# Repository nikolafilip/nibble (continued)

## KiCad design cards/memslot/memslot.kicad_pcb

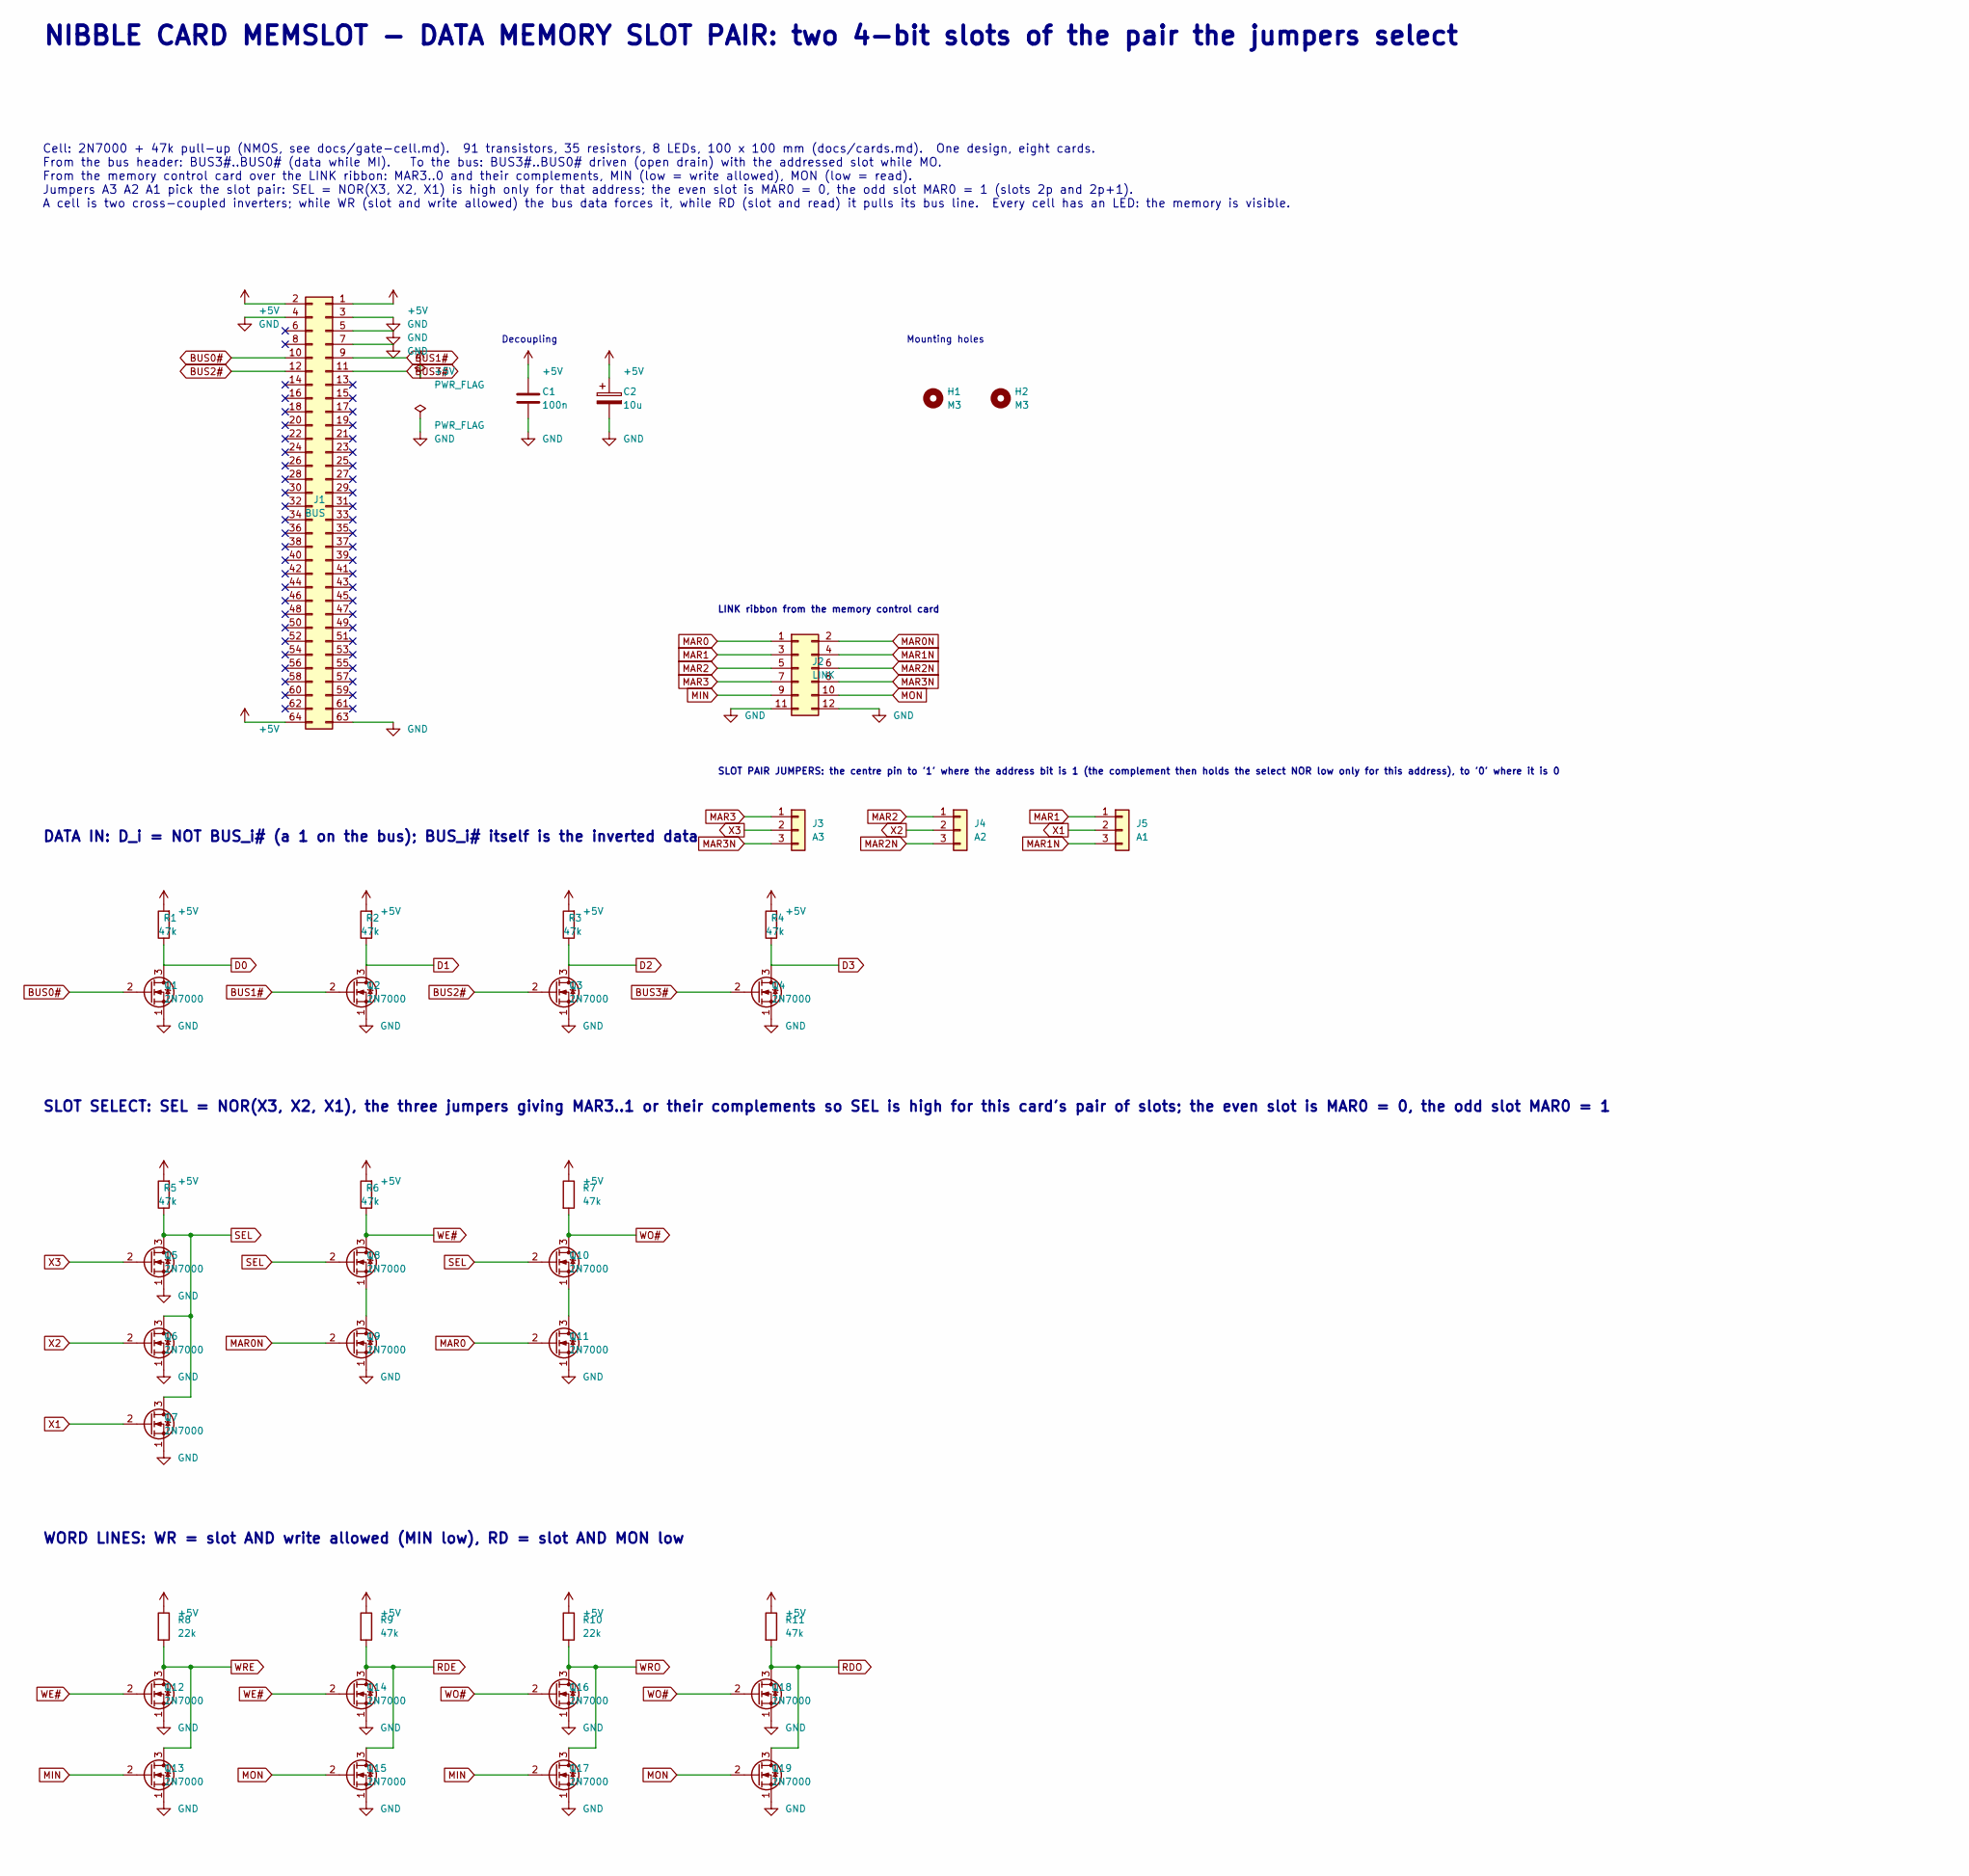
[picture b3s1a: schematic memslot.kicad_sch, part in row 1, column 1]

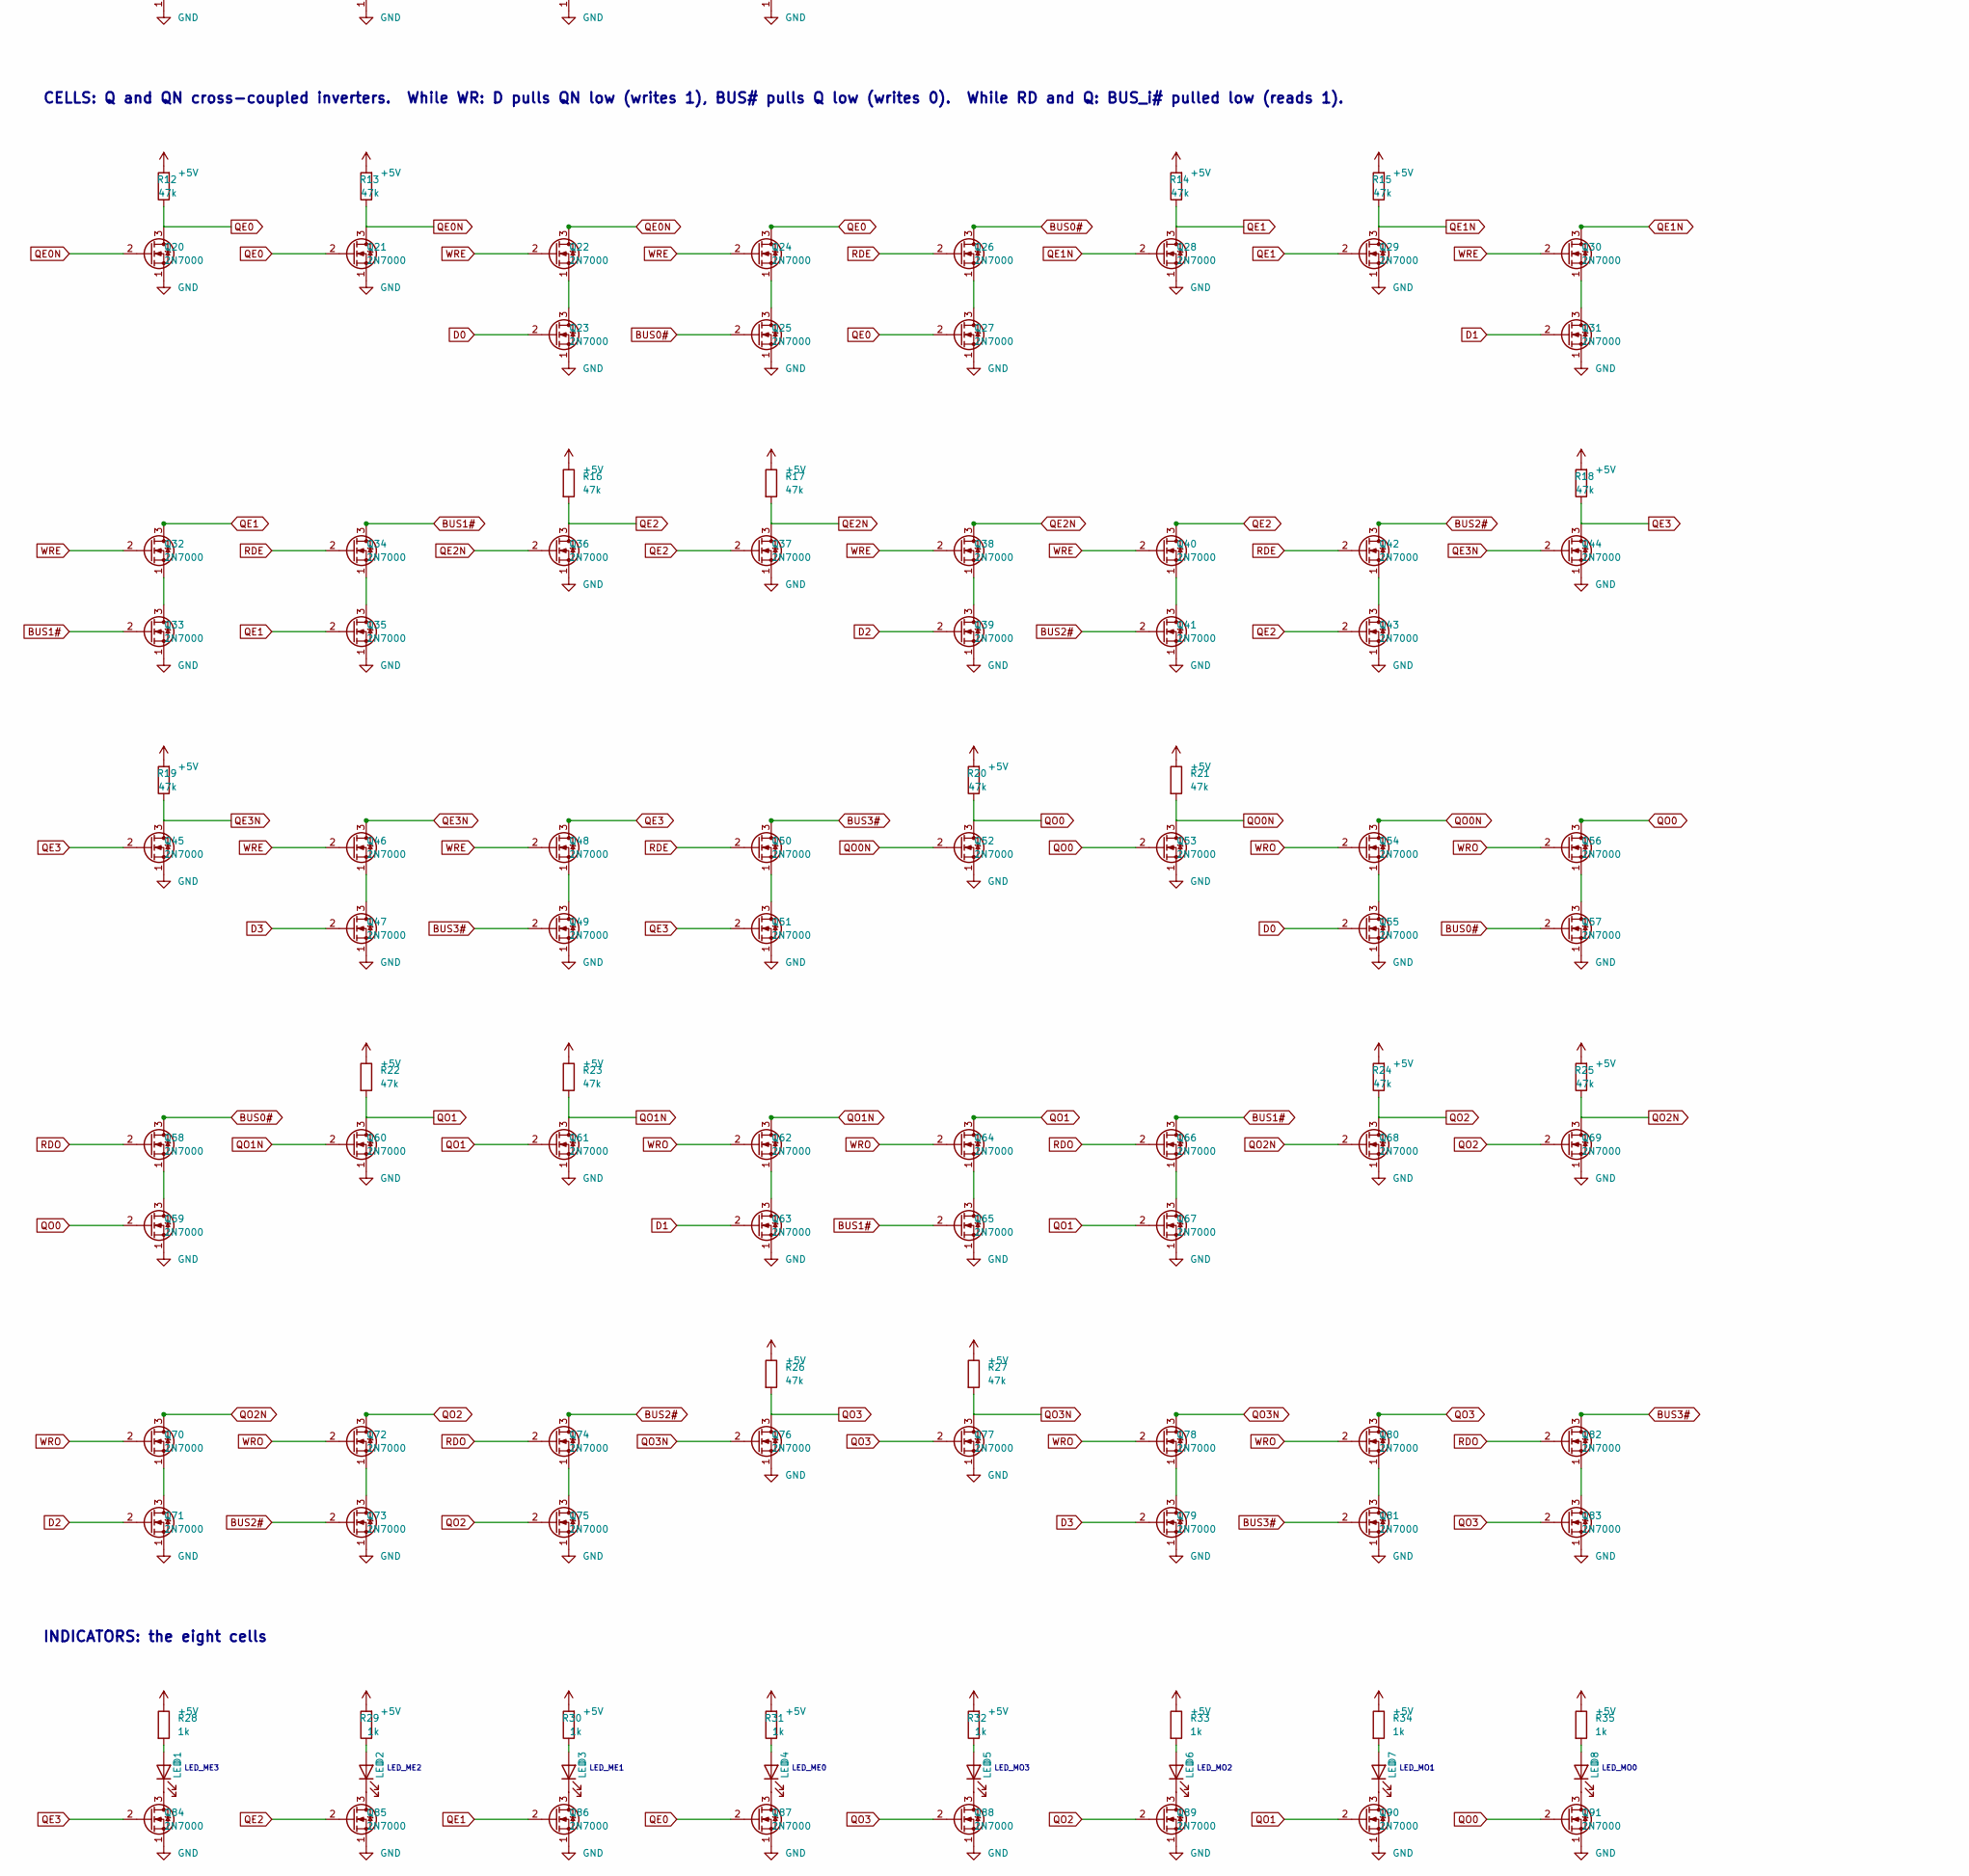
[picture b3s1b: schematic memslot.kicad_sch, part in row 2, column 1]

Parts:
C1: 100n; C_Disc_D5.0mm_W2.5mm_P2.50mm
C2: 10u; CP_Radial_D5.0mm_P2.00mm
D1, D2, D3, D4, D5, D6, D7, D8: LED; LED_D3.0mm
H1, H2: M3; MountingHole_3.2mm_M3_Pad
J1: BUS; IDC-Header_2x32_P2.54mm_Vertical
J2: LINK; IDC-Header_2x06_P2.54mm_Vertical
J3: A3; PinHeader_1x03_P2.54mm_Vertical
J4: A2; PinHeader_1x03_P2.54mm_Vertical
J5: A1; PinHeader_1x03_P2.54mm_Vertical
Q1, Q2, Q3, Q4, Q5, Q6, Q7, Q8, Q9, Q10, Q11, Q12, Q13, Q14, Q15, Q16, Q17, Q18, Q19, Q20, Q21, Q22, Q23, Q24, Q25, Q26, Q27, Q28, Q29, Q30, Q31, Q32, Q33, Q34, Q35, Q36, Q37, Q38, Q39, Q40, Q41, Q42, Q43, Q44, Q45, Q46, Q47, Q48, Q49, Q50, Q51, Q52, Q53, Q54, Q55, Q56, Q57, Q58, Q59, Q60, Q61, Q62, Q63, Q64, Q65, Q66, Q67, Q68, Q69, Q70, Q71, Q72, Q73, Q74, Q75, Q76, Q77, Q78, Q79, Q80, Q81, Q82, Q83, Q84, Q85, Q86, Q87, Q88, Q89, Q90, Q91: 2N7000; TO-92_Inline_Wide
R1, R2, R3, R4, R5, R6, R7, R9, R11, R12, R13, R14, R15, R16, R17, R18, R19, R20, R21, R22, R23, R24, R25, R26, R27: 47k; R_Axial_DIN0207_L6.3mm_D2.5mm_P5.08mm_Vertical
R8, R10: 22k; R_Axial_DIN0207_L6.3mm_D2.5mm_P5.08mm_Vertical
R28, R29, R30, R31, R32, R33, R34, R35: 1k; R_Axial_DIN0207_L6.3mm_D2.5mm_P5.08mm_Vertical

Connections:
+5V: C1.1, C2.1, J1.1, J1.2, J1.64, R1.2, R2.2, R3.2, R4.2, R5.2, R6.2, R7.1, R8.1, R9.1, R10.1, R11.1, R12.2, R13.2, R14.2, R15.2, R16.1, R17.1, R18.2, R19.2, R20.2, R21.1, R22.1, R23.1, R24.2, R25.2, R26.1, R27.1, R28.1, R29.2, R30.2, R31.2, R32.2, R33.1, R34.1, R35.1
BUS0#: J1.10, Q1.2 (G), Q25.2 (G), Q26.3 (D), Q57.2 (G), Q58.3 (D)
BUS1#: J1.9, Q2.2 (G), Q33.2 (G), Q34.3 (D), Q65.2 (G), Q66.3 (D)
BUS2#: J1.12, Q3.2 (G), Q41.2 (G), Q42.3 (D), Q73.2 (G), Q74.3 (D)
BUS3#: J1.11, Q4.2 (G), Q49.2 (G), Q50.3 (D), Q81.2 (G), Q82.3 (D)
D0: Q1.3 (D), Q23.2 (G), Q55.2 (G), R1.1
D1: Q2.3 (D), Q31.2 (G), Q63.2 (G), R2.1
D2: Q3.3 (D), Q39.2 (G), Q71.2 (G), R3.1
D3: Q4.3 (D), Q47.2 (G), Q79.2 (G), R4.1
GND: C1.2, C2.2, J1.3, J1.4, J1.5, J1.7, J1.63, J2.11, J2.12, Q1.1 (S), Q2.1 (S), Q3.1 (S), Q4.1 (S), Q5.1 (S), Q6.1 (S), Q7.1 (S), Q9.1 (S), Q11.1 (S), Q12.1 (S), Q13.1 (S), Q14.1 (S), Q15.1 (S), Q16.1 (S), Q17.1 (S), Q18.1 (S), Q19.1 (S), Q20.1 (S), Q21.1 (S), Q23.1 (S), Q25.1 (S), Q27.1 (S), Q28.1 (S), Q29.1 (S), Q31.1 (S), Q33.1 (S), Q35.1 (S), Q36.1 (S), Q37.1 (S), Q39.1 (S), Q41.1 (S), Q43.1 (S), Q44.1 (S), Q45.1 (S), Q47.1 (S), Q49.1 (S), Q51.1 (S), Q52.1 (S), Q53.1 (S), Q55.1 (S), Q57.1 (S), Q59.1 (S), Q60.1 (S), Q61.1 (S), Q63.1 (S), Q65.1 (S), Q67.1 (S), Q68.1 (S), Q69.1 (S), Q71.1 (S), Q73.1 (S), Q75.1 (S), Q76.1 (S), Q77.1 (S), Q79.1 (S), Q81.1 (S), Q83.1 (S), Q84.1 (S), Q85.1 (S), Q86.1 (S), Q87.1 (S), Q88.1 (S), Q89.1 (S), Q90.1 (S), Q91.1 (S)
MAR0: J2.1, Q11.2 (G)
MAR0N: J2.2, Q9.2 (G)
MAR1: J2.3, J5.1
MAR1N: J2.4, J5.3
MAR2: J2.5, J4.1
MAR2N: J2.6, J4.3
MAR3: J2.7, J3.1
MAR3N: J2.8, J3.3
MIN: J2.9, Q13.2 (G), Q17.2 (G)
MON: J2.10, Q15.2 (G), Q19.2 (G)
unnamed: D1.2 (A), R28.2
unnamed: D1.1 (K), Q84.3 (D)
unnamed: D2.2 (A), R29.1
unnamed: D2.1 (K), Q85.3 (D)
unnamed: D3.2 (A), R30.1
unnamed: D3.1 (K), Q86.3 (D)
unnamed: D4.2 (A), R31.1
unnamed: D4.1 (K), Q87.3 (D)
unnamed: D5.2 (A), R32.1
unnamed: D5.1 (K), Q88.3 (D)
unnamed: D6.2 (A), R33.2
unnamed: D6.1 (K), Q89.3 (D)
unnamed: D7.2 (A), R34.2
unnamed: D7.1 (K), Q90.3 (D)
unnamed: D8.2 (A), R35.2
unnamed: D8.1 (K), Q91.3 (D)
unnamed: Q8.1 (S), Q9.3 (D)
unnamed: Q10.1 (S), Q11.3 (D)
unnamed: Q22.1 (S), Q23.3 (D)
unnamed: Q24.1 (S), Q25.3 (D)
unnamed: Q26.1 (S), Q27.3 (D)
unnamed: Q30.1 (S), Q31.3 (D)
unnamed: Q32.1 (S), Q33.3 (D)
unnamed: Q34.1 (S), Q35.3 (D)
unnamed: Q38.1 (S), Q39.3 (D)
unnamed: Q40.1 (S), Q41.3 (D)
unnamed: Q42.1 (S), Q43.3 (D)
unnamed: Q46.1 (S), Q47.3 (D)
unnamed: Q48.1 (S), Q49.3 (D)
unnamed: Q50.1 (S), Q51.3 (D)
unnamed: Q54.1 (S), Q55.3 (D)
unnamed: Q56.1 (S), Q57.3 (D)
unnamed: Q58.1 (S), Q59.3 (D)
unnamed: Q62.1 (S), Q63.3 (D)
unnamed: Q64.1 (S), Q65.3 (D)
unnamed: Q66.1 (S), Q67.3 (D)
unnamed: Q70.1 (S), Q71.3 (D)
unnamed: Q72.1 (S), Q73.3 (D)
unnamed: Q74.1 (S), Q75.3 (D)
unnamed: Q78.1 (S), Q79.3 (D)
unnamed: Q80.1 (S), Q81.3 (D)
unnamed: Q82.1 (S), Q83.3 (D)
QE0: Q20.3 (D), Q21.2 (G), Q24.3 (D), Q27.2 (G), Q87.2 (G), R12.1
QE0N: Q20.2 (G), Q21.3 (D), Q22.3 (D), R13.1
QE1: Q28.3 (D), Q29.2 (G), Q32.3 (D), Q35.2 (G), Q86.2 (G), R14.1
QE1N: Q28.2 (G), Q29.3 (D), Q30.3 (D), R15.1
QE2: Q36.3 (D), Q37.2 (G), Q40.3 (D), Q43.2 (G), Q85.2 (G), R16.2
QE2N: Q36.2 (G), Q37.3 (D), Q38.3 (D), R17.2
QE3: Q44.3 (D), Q45.2 (G), Q48.3 (D), Q51.2 (G), Q84.2 (G), R18.1
QE3N: Q44.2 (G), Q45.3 (D), Q46.3 (D), R19.1
QO0: Q52.3 (D), Q53.2 (G), Q56.3 (D), Q59.2 (G), Q91.2 (G), R20.1
QO0N: Q52.2 (G), Q53.3 (D), Q54.3 (D), R21.2
QO1: Q60.3 (D), Q61.2 (G), Q64.3 (D), Q67.2 (G), Q90.2 (G), R22.2
QO1N: Q60.2 (G), Q61.3 (D), Q62.3 (D), R23.2
QO2: Q68.3 (D), Q69.2 (G), Q72.3 (D), Q75.2 (G), Q89.2 (G), R24.1
QO2N: Q68.2 (G), Q69.3 (D), Q70.3 (D), R25.1
QO3: Q76.3 (D), Q77.2 (G), Q80.3 (D), Q83.2 (G), Q88.2 (G), R26.2
QO3N: Q76.2 (G), Q77.3 (D), Q78.3 (D), R27.2
RDE: Q14.3 (D), Q15.3 (D), Q26.2 (G), Q34.2 (G), Q42.2 (G), Q50.2 (G), R9.2
RDO: Q18.3 (D), Q19.3 (D), Q58.2 (G), Q66.2 (G), Q74.2 (G), Q82.2 (G), R11.2
SEL: Q5.3 (D), Q6.3 (D), Q7.3 (D), Q8.2 (G), Q10.2 (G), R5.1
WE#: Q8.3 (D), Q12.2 (G), Q14.2 (G), R6.1
WO#: Q10.3 (D), Q16.2 (G), Q18.2 (G), R7.2
WRE: Q12.3 (D), Q13.3 (D), Q22.2 (G), Q24.2 (G), Q30.2 (G), Q32.2 (G), Q38.2 (G), Q40.2 (G), Q46.2 (G), Q48.2 (G), R8.2
WRO: Q16.3 (D), Q17.3 (D), Q54.2 (G), Q56.2 (G), Q62.2 (G), Q64.2 (G), Q70.2 (G), Q72.2 (G), Q78.2 (G), Q80.2 (G), R10.2
X1: J5.2, Q7.2 (G)
X2: J4.2, Q6.2 (G)
X3: J3.2, Q5.2 (G)

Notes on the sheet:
NIBBLE CARD MEMSLOT - DATA MEMORY SLOT PAIR: two 4-bit slots of the pair the jumpers select
Cell: 2N7000 + 47k pull-up (NMOS, see docs/gate-cell.md). 91 transistors, 35 resistors, 8 LEDs, 100 x 100 mm (docs/cards.md). One design, eight cards. From the bus header: BUS3#..BUS0# (data while MI). To the bus: BUS3#..BUS0# driven (open drain) with the addressed slot while MO. From the memory co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
DATA IN: D_i = NOT BUS_i# (a 1 on the bus); BUS_i# itself is the inverted data
SLOT SELECT: SEL = NOR(X3, X2, X1), the three jumpers giving MAR3..1 or their complements so SEL is high for this card's pair of slots; the even slot is MAR0 = 0, the odd slot MAR0 = 1
WORD LINES: WR = slot AND write allowed (MIN low), RD = slot AND MON low
CELLS: Q and QN cross-coupled inverters. While WR: D pulls QN low (writes 1), BUS# pulls Q low (writes 0). While RD and Q: BUS_i# pulled low (reads 1).
INDICATORS: the eight cells
LED_ME3
LED_ME2
LED_ME1
LED_ME0
LED_MO3
LED_MO2
LED_MO1
LED_MO0
Decoupling
Mounting holes
LINK ribbon from the memory control card
SLOT PAIR JUMPERS: the centre pin to '1' where the address bit is 1 (the complement then holds the select NOR low only for this address), to '0' where it is 0

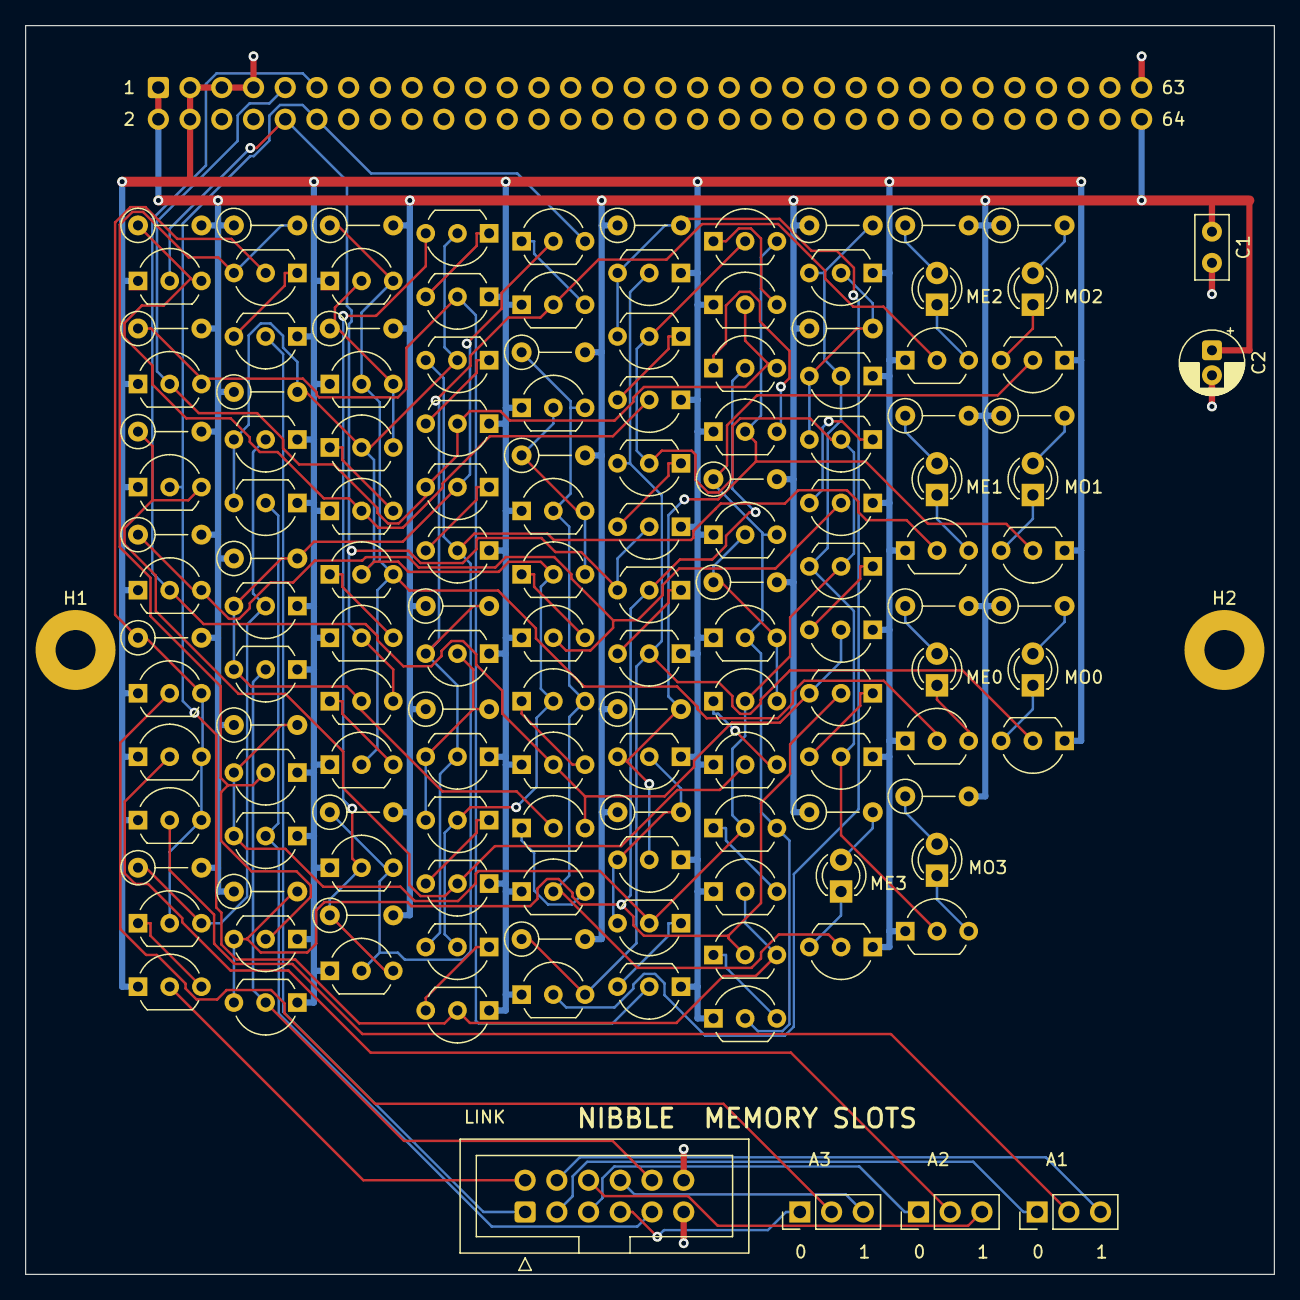
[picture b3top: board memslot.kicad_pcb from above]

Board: 2 copper layers, 100.0 x 100.0 mm, 143 parts (1 on the bottom side), 88 nets.
